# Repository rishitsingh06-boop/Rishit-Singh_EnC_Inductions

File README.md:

# Project Kratos development environment
For people who can't set up Ubuntu 22
---

## Quick Start

### Linux

```bash
# One-time setup (installs Docker, GPU toolkit, pulls image, installs CLI)
chmod +x setup.sh kratos
./setup.sh

# Start the environment
kratos start

# Open the desktop in your browser
# → http://localhost:6080/vnc.html

# Open a terminal inside the container
kratos shell

# Stop when done
kratos stop
```

### macOS

```bash
# One-time setup (installs Docker Desktop, Genesis venv, CLI)
chmod +x setup_mac.sh kratos
./setup_mac.sh

# Start (also activates Genesis venv automatically)
kratos start

# Desktop: http://localhost:6080/vnc.html
# Genesis bridge: python adapters/genesis_bridge.py
```

---

## What You Get

| Port | Service | What it does |
|------|---------|-------------|
| 6080 | noVNC | Full Linux desktop in your browser (RViz2, Gazebo, rqt) |
| 9090 | rosbridge | WebSocket bridge so macOS Genesis can talk to ROS2 |

### Inside the Container

Everything is pre-installed and ready:

```bash
# Launch TurtleBot3 in Gazebo
ros2 launch turtlebot3_gazebo turtlebot3_world.launch.py

# Open RViz2 (in another terminal: kratos shell)
rviz2

# Teleop keyboard control
ros2 run turtlebot3_teleop teleop_keyboard

# Launch Nav2 navigation
ros2 launch turtlebot3_navigation2 navigation2.launch.py use_sim_time:=true map:=/path/to/map.yaml

# See all running topics
ros2 topic list

# RQT tools
rqt
rqt_graph
```

### Your Workspace

- Host: `~/ros2_ws/` → Container: `/workspace/`
- Files you create on either side appear on both
- Files are owned by **your user** (not root)

```bash
# Build your own ROS2 packages inside the container
cd /workspace
mkdir -p src
# put your packages in src/
colcon build
source install/setup.bash
```

---

## Commands

```
kratos start    Start the dev container + noVNC desktop
kratos stop     Stop the dev container
kratos status   Check if the container is running
kratos shell    Open a bash shell inside the container (ROS2 pre-sourced)
```

---

## Troubleshooting

**"Permission denied" on docker commands**
```bash
sudo usermod -aG docker $USER
newgrp docker    # or log out and back in
```
**Apt can't find any package**
```bash
sudo apt update
sudo apt install [package]
```

**Container starts but noVNC doesn't load**
```bash
./kratos-env.sh status     # is it running?
docker logs kratos_dev     # check for errors
```

**"kratos-env.sh: command not found"**
```bash
# Either run from the repo directory:
./kratos-env.sh start

# Or install to PATH:
sudo cp kratos-env.sh /usr/local/bin/kratos
```

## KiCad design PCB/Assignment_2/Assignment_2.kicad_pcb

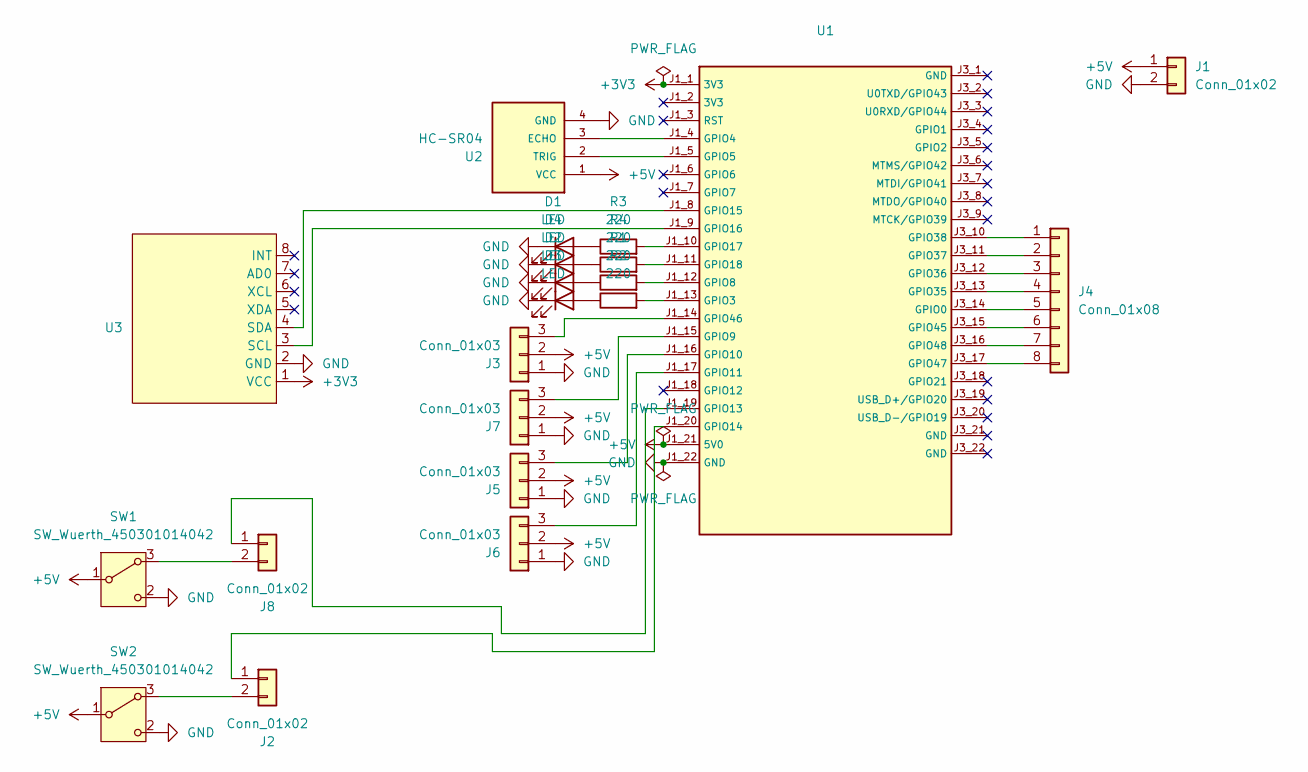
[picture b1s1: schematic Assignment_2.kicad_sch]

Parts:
D1, D2, D3, D4: LED; LED_D5.0mm
J1, J2, J8: Conn_01x02; PinHeader_1x02_P2.54mm_Vertical
J3, J5, J6, J7: Conn_01x03; FanPinHeader_1x03_P2.54mm_Vertical
J4: Conn_01x08; PinHeader_1x08_P2.54mm_Vertical
R1, R2, R3, R4: 220; R_Axial_DIN0207_L6.3mm_D2.5mm_P7.62mm_Horizontal
SW1, SW2: SW_Wuerth_450301014042; SW_Slide-03_Wuerth-WS-SLTV_10x2.5x6.4_P2.54mm
U1: MODULE_ESP32-S3-DEVKITC-1U-N8R8
U2: HC-SR04; XCVR_HC-SR04
U3: MODULE_GY-521

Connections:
+3V3: U1.J1_1 (3V3), U3.1 (VCC)
+5V: J1.1, J3.2, J5.2, J6.2, J7.2, SW1.1 (B), SW2.1 (B), U1.J1_21 (5V0), U2.1 (VCC)
GND: D1.1 (K), D2.1 (K), D3.1 (K), D4.1 (K), J1.2, J3.1, J5.1, J6.1, J7.1, SW1.2 (C), SW2.2 (C), U1.J1_22 (GND), U2.4 (GND), U3.2 (GND)
unnamed: D1.2 (A), R3.1
unnamed: D2.2 (A), R1.1
unnamed: D3.2 (A), R2.1
unnamed: D4.2 (A), R4.1
unnamed: J2.1, U1.J1_20 (GPIO14)
unnamed: J2.2, SW2.3 (A)
unnamed: J3.3, U1.J1_14 (GPIO46)
unnamed: J4.1, U1.J3_10 (GPIO38)
unnamed: J4.2, U1.J3_11 (GPIO37)
unnamed: J4.3, U1.J3_12 (GPIO36)
unnamed: J4.4, U1.J3_13 (GPIO35)
unnamed: J4.5, U1.J3_14 (GPIO0)
unnamed: J4.6, U1.J3_15 (GPIO45)
unnamed: J4.7, U1.J3_16 (GPIO48)
unnamed: J4.8, U1.J3_17 (GPIO47)
unnamed: J5.3, U1.J1_16 (GPIO10)
unnamed: J6.3, U1.J1_17 (GPIO11)
unnamed: J7.3, U1.J1_15 (GPIO9)
unnamed: J8.1, U1.J1_19 (GPIO13)
unnamed: J8.2, SW1.3 (A)
unnamed: R2.2, U1.J1_13 (GPIO3)
unnamed: U1.J1_4 (GPIO4), U2.3 (ECHO)
unnamed: U1.J1_5 (GPIO5), U2.2 (TRIG)
unnamed: R1.2, U1.J1_12 (GPIO8)
unnamed: U1.J1_8 (GPIO15), U3.4 (SDA)
unnamed: U1.J1_9 (GPIO16), U3.3 (SCL)
unnamed: R3.2, U1.J1_10 (GPIO17)
unnamed: R4.2, U1.J1_11 (GPIO18)

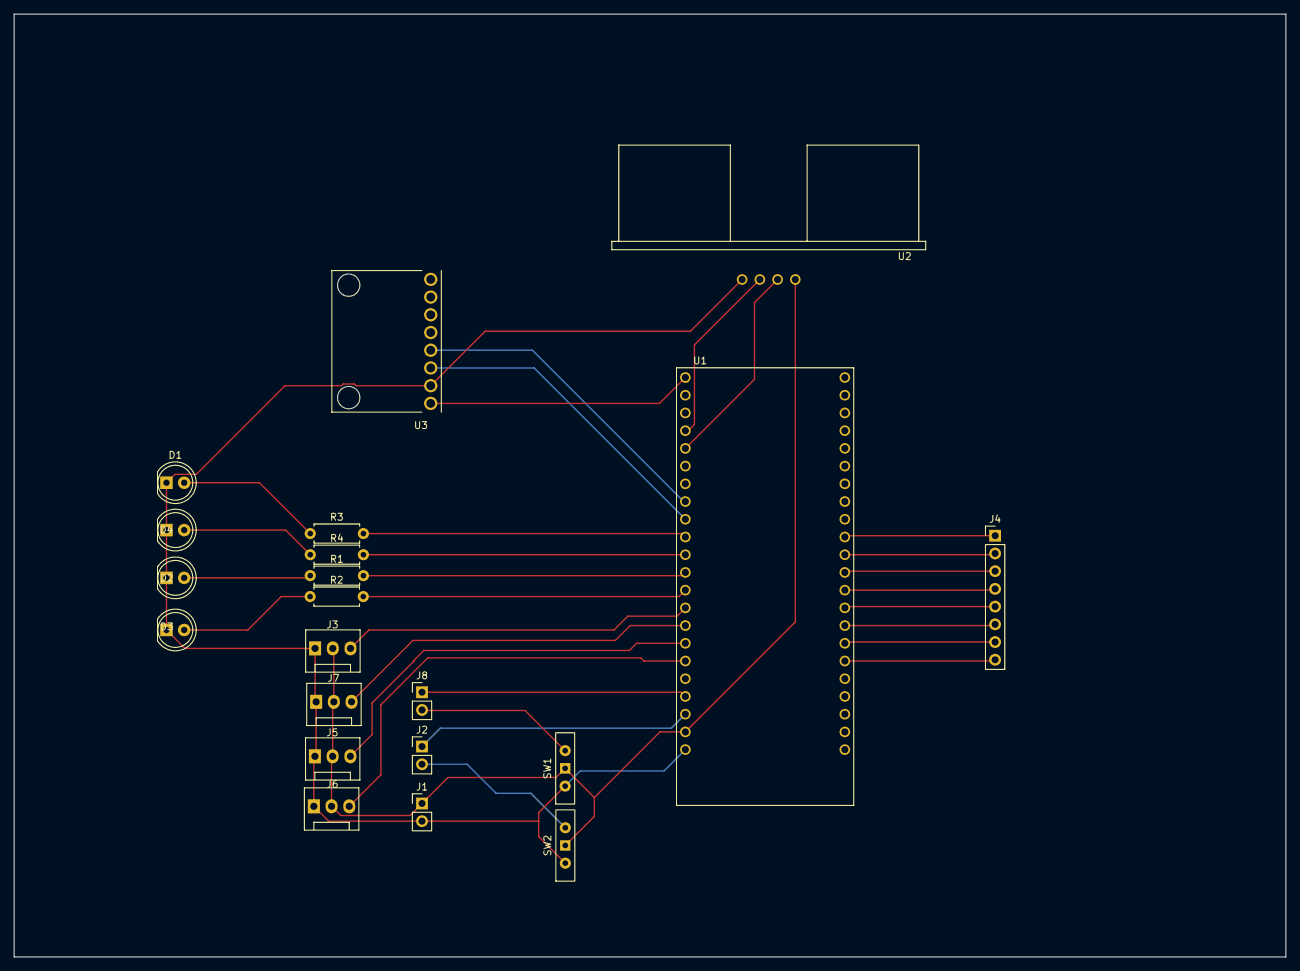
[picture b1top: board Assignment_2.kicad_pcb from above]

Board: 2 copper layers, 182.3 x 135.2 mm, 21 parts (0 on the bottom side), 31 nets.

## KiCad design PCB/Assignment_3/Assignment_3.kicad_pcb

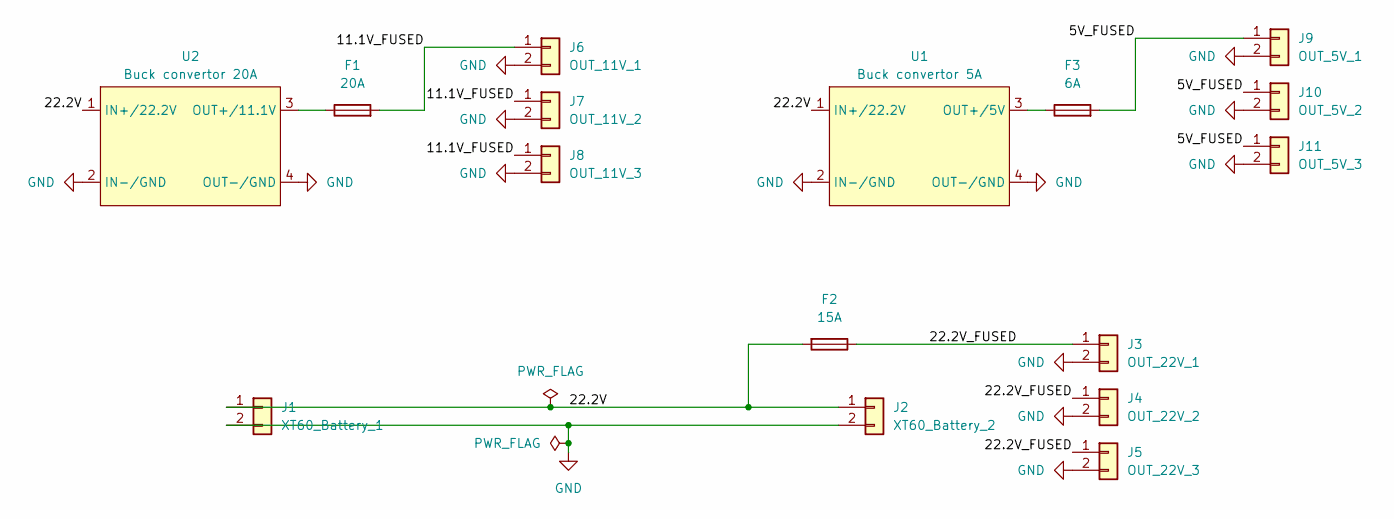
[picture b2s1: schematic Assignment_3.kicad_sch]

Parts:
F1: 20A; Fuseholder_Cylinder-5x20mm_Schurter_0031_8201_Horizontal_Op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
F2: 15A; Fuseholder_Cylinder-5x20mm_Schurter_0031_8201_Horizontal_Op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
F3: 6A; Fuseholder_Cylinder-5x20mm_Schurter_0031_8201_Horizontal_Op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
J1: XT60_Battery_1; AMASS_XT60-F_1x02_P7.20mm_Vertical
J2: XT60_Battery_2; AMASS_XT60-M_1x02_P7.20mm_Vertical
J3: OUT_22V_1; TerminalBlock_CUI_TB007-508-02_1x02_P5.08mm_Horizontal
J4: OUT_22V_2; TerminalBlock_CUI_TB007-508-02_1x02_P5.08mm_Horizontal
J5: OUT_22V_3; TerminalBlock_CUI_TB007-508-02_1x02_P5.08mm_Horizontal
J6: OUT_11V_1; TerminalBlock_CUI_TB007-508-02_1x02_P5.08mm_Horizontal
J7: OUT_11V_2; TerminalBlock_CUI_TB007-508-02_1x02_P5.08mm_Horizontal
J8: OUT_11V_3; TerminalBlock_CUI_TB007-508-02_1x02_P5.08mm_Horizontal
J9: OUT_5V_1; TerminalBlock_CUI_TB007-508-02_1x02_P5.08mm_Horizontal
J10: OUT_5V_2; TerminalBlock_CUI_TB007-508-02_1x02_P5.08mm_Horizontal
J11: OUT_5V_3; TerminalBlock_CUI_TB007-508-02_1x02_P5.08mm_Horizontal
U1: Buck convertor 5A; BUCK_5A
U2: Buck convertor 20A; BUCK_20A

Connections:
/5V_FUSED: F3.2, J9.1, J10.1, J11.1
/11.1V_FUSED: F1.2, J6.1, J7.1, J8.1
/22.2V: F2.2, J1.1, J2.1, U1.1 (IN+/22.2V), U2.1 (IN+/22.2V)
/22.2V_FUSED: F2.1, J3.1, J4.1, J5.1
GND: J1.2, J2.2, J3.2, J4.2, J5.2, J6.2, J7.2, J8.2, J9.2, J10.2, J11.2, U1.2 (IN-/GND), U1.4 (OUT-/GND), U2.2 (IN-/GND), U2.4 (OUT-/GND)
unnamed: F3.1, U1.3 (OUT+/5V)
unnamed: F1.1, U2.3 (OUT+/11.1V)

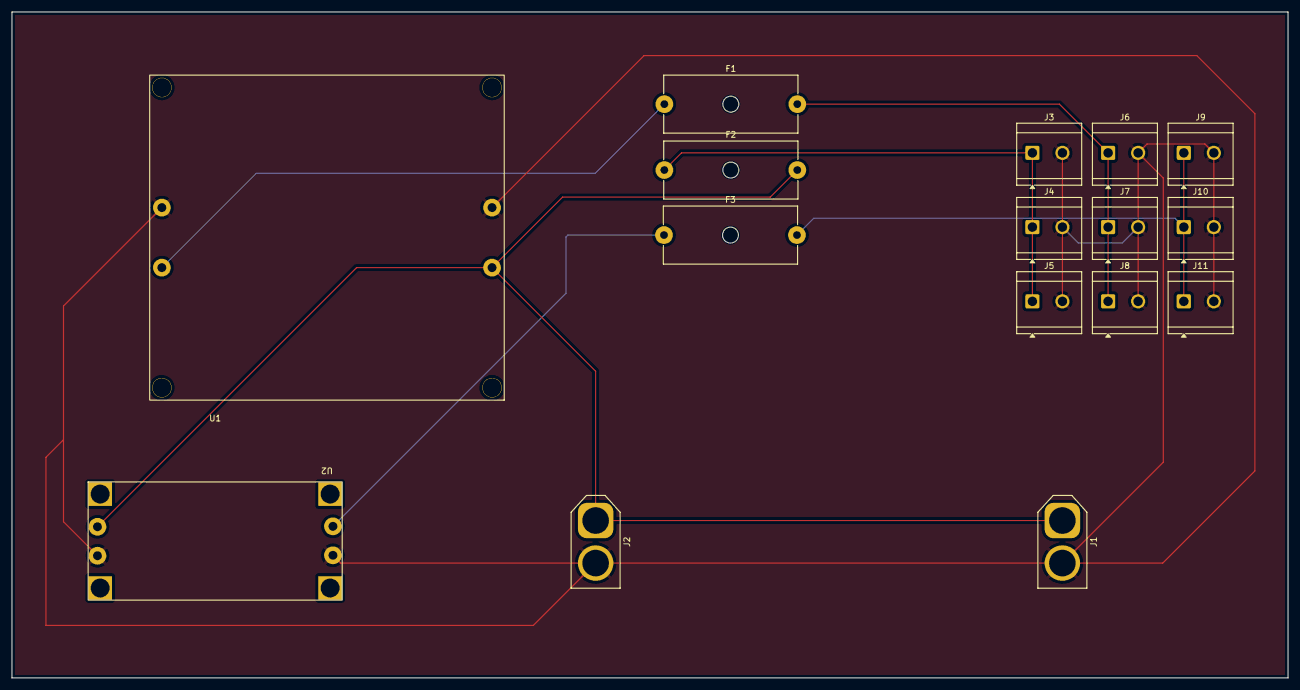
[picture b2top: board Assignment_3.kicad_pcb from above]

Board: 2 copper layers, 216.0 x 112.7 mm, 16 parts (0 on the bottom side), 7 nets.

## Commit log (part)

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2026-06-13 fix: update all references from ./kratos to ./kratos-env.sh
2026-06-13 fixed legacy nvidia flags
2026-06-13 minor skill issue, all good
2026-06-13 feat: use ~/ros2_ws instead of ~/kratos_ws for file sharing
2026-06-13 docs: clean up stale kratos references, add apt update troubleshooting
2026-06-13 cleaner readme
2026-06-29 Added joint_state_publisher for enc assignment use
2026-06-29 Initial submission
